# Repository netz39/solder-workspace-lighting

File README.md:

# solder workspace lighting
*Created with KiCad 5.1.9*

Dieses Repo beinhaltet die drei notwendigen Platinen, um den Lötarbeitsplatz im Netz39 ordentlich auszuleuchten.

## central_control
Überwacht die Temperatur aller LED-Projektoren und betreibt PWM-Dimming. Desweiteren bietet die Platine mehrere Schnittstellen (UART, SPI, I²C, CAN) für Erweiterungen an

## constant_current_source
Ein Buck-Converter liefert den voreingestellten konstanten Strom für die LEDs.

## high_power_LED:
Bestückt mit HighPower-LEDs, Thermistor und Kühlkörper.

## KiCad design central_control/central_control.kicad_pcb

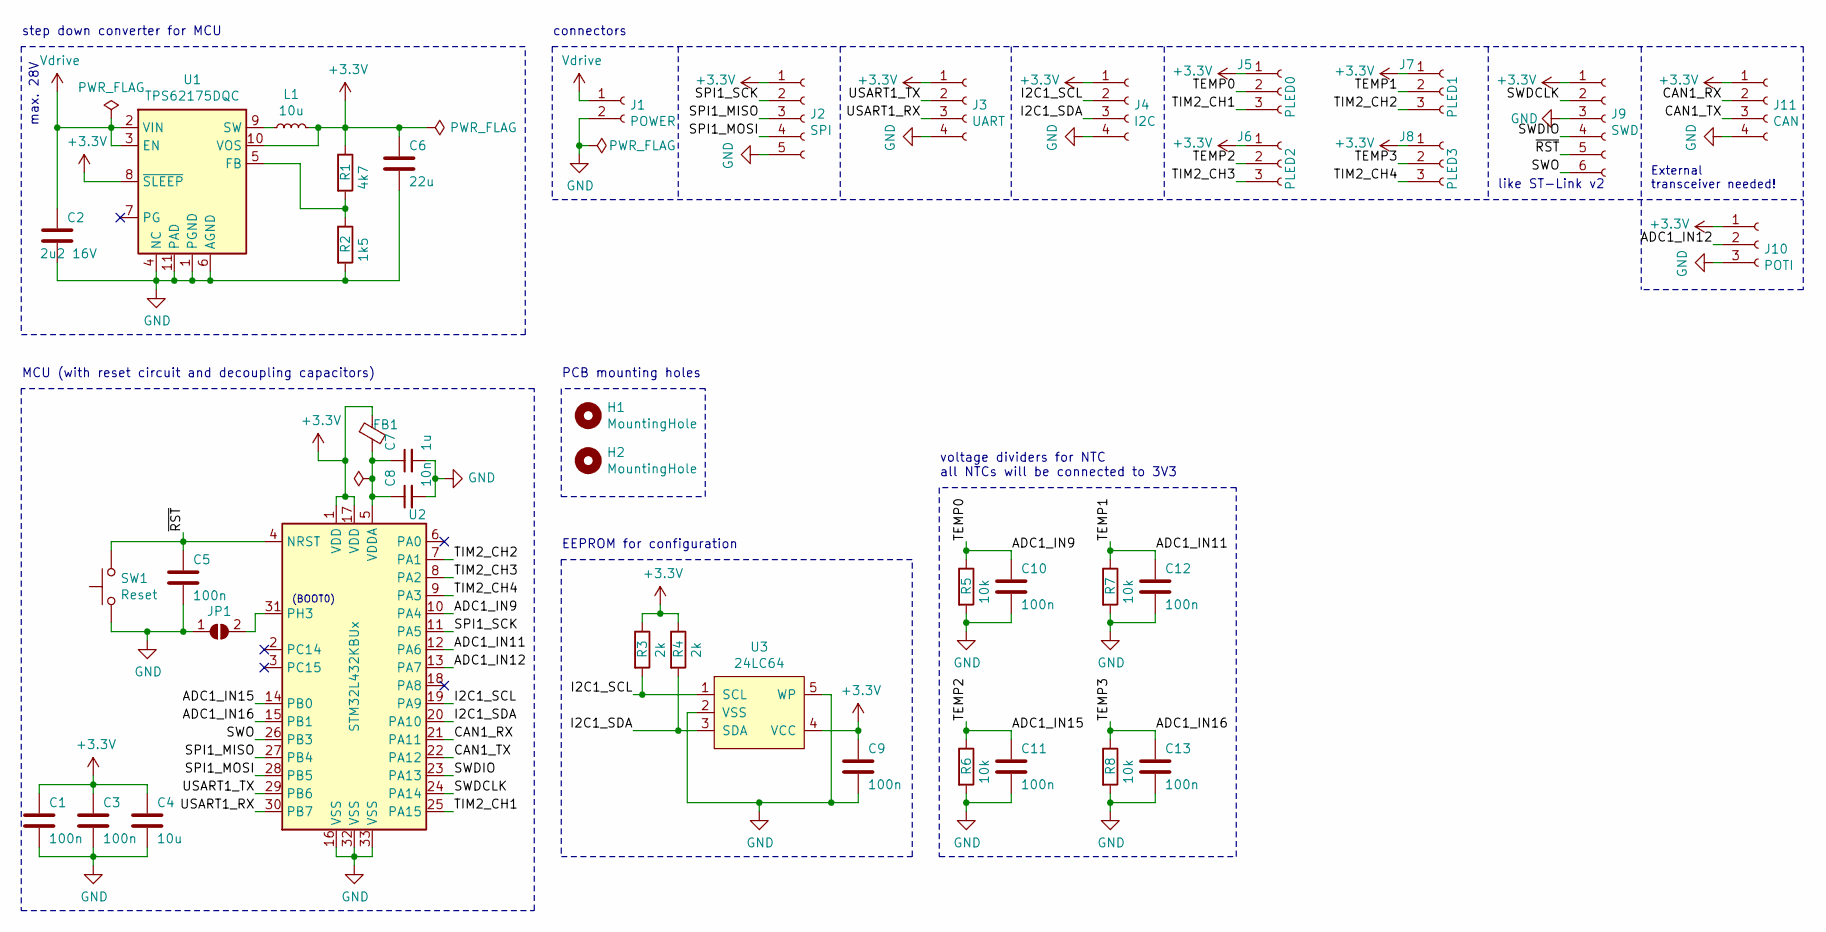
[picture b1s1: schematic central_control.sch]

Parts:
C1, C3, C5, C9, C10, C11, C12, C13: 100n; C_0603_1608Metric
C2: 2u2 16V; C_0603_1608Metric
C4: 10u; C_0805_2012Metric
C6: 22u; C_0805_2012Metric
C7: 1u; C_0603_1608Metric
C8: 10n; C_0603_1608Metric
FB1: Ferrite_Bead_Small; R_0603_1608Metric
H1, H2: MountingHole; MountingHole_2.7mm_M2.5_ISO14580
J1: POWER; Molex_PicoBlade_53047-0210_1x02_P1.25mm_Vertical
J2: SPI; Molex_PicoBlade_53047-0510_1x05_P1.25mm_Vertical
J3: UART; Molex_PicoBlade_53047-0410_1x04_P1.25mm_Vertical
J4: I2C; Molex_PicoBlade_53047-0410_1x04_P1.25mm_Vertical
J5: PLED0; Molex_PicoBlade_53047-0310_1x03_P1.25mm_Vertical
J6: PLED2; Molex_PicoBlade_53047-0310_1x03_P1.25mm_Vertical
J7: PLED1; Molex_PicoBlade_53047-0310_1x03_P1.25mm_Vertical
J8: PLED3; Molex_PicoBlade_53047-0310_1x03_P1.25mm_Vertical
J9: SWD; PinHeader_1x06_P2.54mm_Vertical
J10: POTI; Molex_PicoBlade_53047-0310_1x03_P1.25mm_Vertical
J11: CAN; Molex_PicoBlade_53047-0410_1x04_P1.25mm_Vertical
JP1: SolderJumper_2_Open; SolderJumper-2_P1.3mm_Open_TrianglePad1.0x1.5mm
L1: 10u; L_1210_3225Metric
R1: 4k7; R_0603_1608Metric
R2: 1k5; R_0603_1608Metric
R3, R4: 2k; R_0603_1608Metric
R5, R6, R7, R8: 10k; R_0603_1608Metric
SW1: SW_Push; PTS636_F-leads
U1: TPS62175DQC; WSON-10-1EP_2x3mm_P0.5mm_EP0.84x2.4mm_ThermalVias
U2: STM32L432KBUx; QFN-32-1EP_5x5mm_P0.5mm_EP3.45x3.45mm
U3: 24LC64; SOT-23-5

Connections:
+3V3: C1.1, C3.1, C4.1, C6.1, C9.1, FB1.1, J2.1, J3.1, J4.1, J5.1, J6.1, J7.1, J8.1, J9.1, J10.1, J11.1, L1.2, R1.1, R3.1, R4.1, U1.8 (~SLEEP), U1.10 (VOS), U2.1 (VDD), U2.17 (VDD), U3.4 (VCC)
/ADC1_IN9: C10.1, J5.2, R5.1, U2.10 (PA4)
/ADC1_IN11: C12.1, J7.2, R7.1, U2.12 (PA6)
/ADC1_IN12: J10.2, U2.13 (PA7)
/ADC1_IN15: C11.1, J6.2, R6.1, U2.14 (PB0)
/ADC1_IN16: C13.1, J8.2, R8.1, U2.15 (PB1)
/CAN1_RX: J11.2, U2.21 (PA11)
/CAN1_TX: J11.3, U2.22 (PA12)
/I2C1_SCL: J4.2, R3.2, U2.19 (PA9), U3.1 (SCL)
/I2C1_SDA: J4.3, R4.2, U2.20 (PA10), U3.3 (SDA)
/SPI1_MISO: J2.3, U2.27 (PB4)
/SPI1_MOSI: J2.4, U2.28 (PB5)
/SPI1_SCK: J2.2, U2.11 (PA5)
/SWDCLK: J9.2, U2.24 (PA14)
/SWDIO: J9.4, U2.23 (PA13)
/SWO: J9.6, U2.26 (PB3)
/TIM2_CH1: J5.3, U2.25 (PA15)
/TIM2_CH2: J7.3, U2.7 (PA1)
/TIM2_CH3: J6.3, U2.8 (PA2)
/TIM2_CH4: J8.3, U2.9 (PA3)
/USART1_RX: J3.3, U2.30 (PB7)
/USART1_TX: J3.2, U2.29 (PB6)
/~RST: C5.1, J9.5, SW1.2, U2.4 (NRST)
GND: C1.2, C2.2, C3.2, C4.2, C5.2, C6.2, C7.2, C8.2, C9.2, C10.2, C11.2, C12.2, C13.2, J1.2, J2.5, J3.4, J4.4, J9.3, J10.3, J11.4, JP1.1 (A), R2.2, R5.2, R6.2, R7.2, R8.2, SW1.1, U1.1 (PGND), U1.4 (NC), U1.6 (AGND), U1.11 (PAD), U2.16 (VSS), U2.32 (VSS), U2.33 (VSS), U3.2 (VSS), U3.5 (WP)
unnamed: C7.1, C8.1, FB1.2, U2.5 (VDDA)
unnamed: JP1.2 (B), U2.31 (PH3)
unnamed: L1.1, U1.9 (SW)
unnamed: R1.2, R2.1, U1.5 (FB)
Vdrive: C2.1, J1.1, U1.2 (VIN), U1.3 (EN)

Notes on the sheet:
max. 28V
step down converter for MCU
MCU (with reset circuit and decoupling capacitors)
connectors
PCB mounting holes
External transceiver needed!
EEPROM for configuration
voltage dividers for NTC all NTCs will be connected to 3V3
like ST-Link v2
(BOOT0)

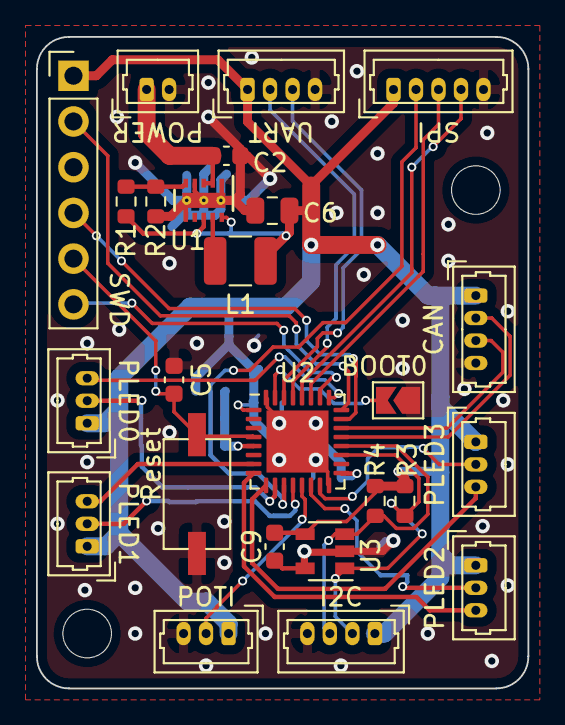
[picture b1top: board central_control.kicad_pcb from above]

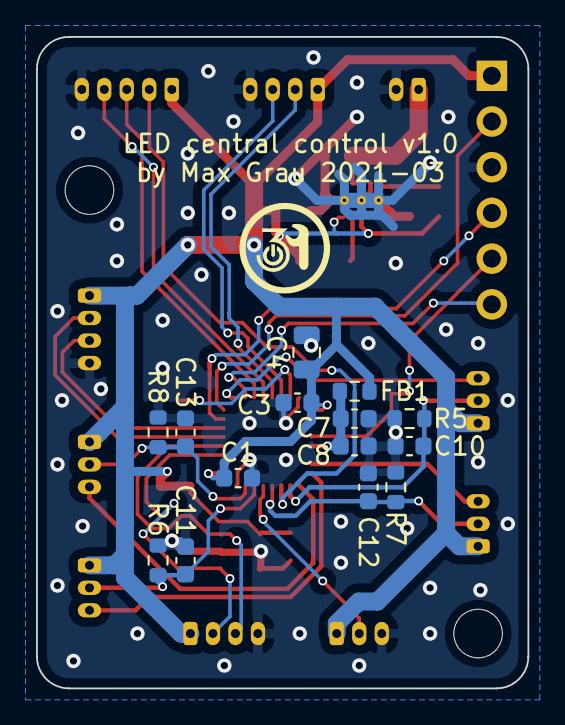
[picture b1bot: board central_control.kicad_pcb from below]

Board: 2 copper layers, 27.3 x 36.2 mm, 42 parts (15 on the bottom side), 29 nets.

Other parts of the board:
svg2mod: G***; netz39-logo

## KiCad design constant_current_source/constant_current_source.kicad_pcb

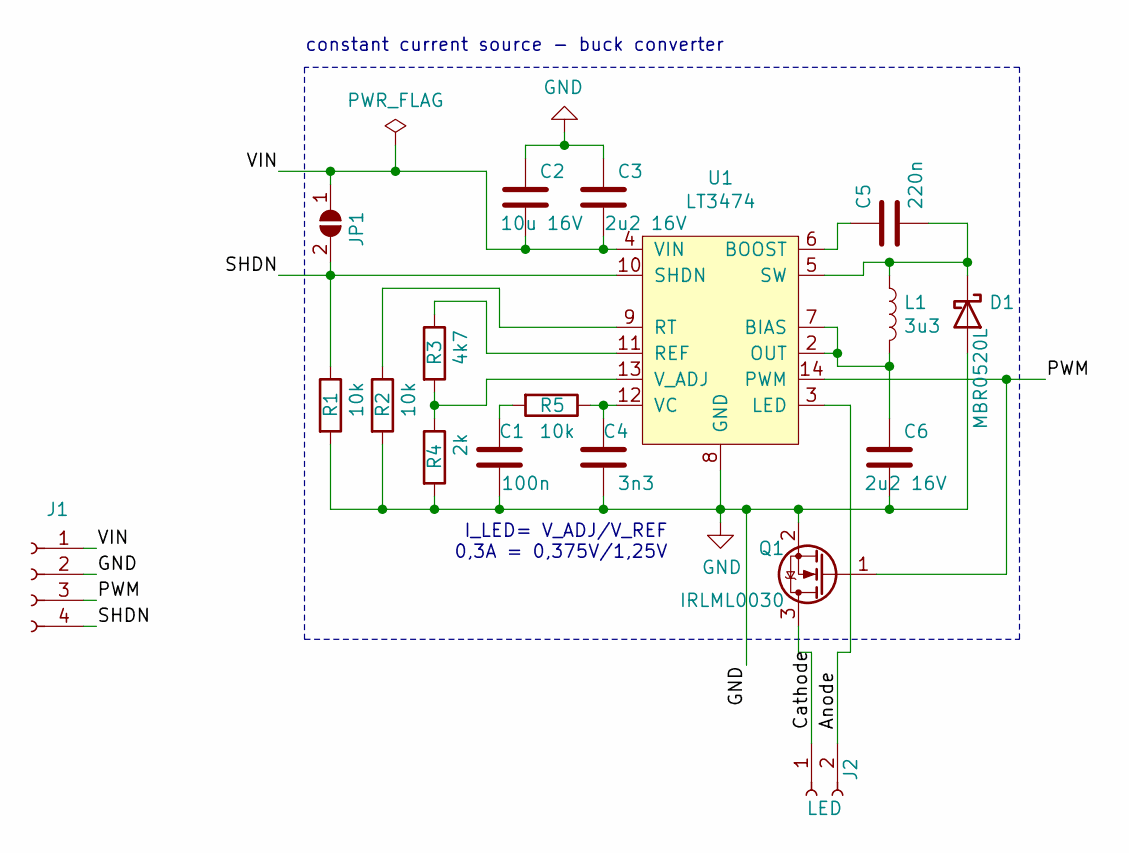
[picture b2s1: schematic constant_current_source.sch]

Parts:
C1: 100n; C_0603_1608Metric
C2: 10u 16V; C_0805_2012Metric
C3, C6: 2u2 16V; C_0603_1608Metric
C4: 3n3; C_0603_1608Metric
C5: 220n; C_0603_1608Metric
D1: MBR0520L; D_SOD-123
J1: Conn; Molex_PicoBlade_53047-0410_1x04_P1.25mm_Vertical
J2: LED; PinHeader_1x02_P2.54mm_Vertical
JP1: SolderJumper_2_Open; SolderJumper-2_P1.3mm_Open_TrianglePad1.0x1.5mm
L1: 3u3; L_Abracon_ASPI-3012S
Q1: IRLML0030; SOT-23
R1, R2, R5: 10k; R_0603_1608Metric
R3: 4k7; R_0603_1608Metric
R4: 2k; R_0603_1608Metric
U1: LT3474; TSSOP-16-1EP_4.4x5mm_P0.65mm

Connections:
/Anode: J2.2, U1.3 (LED)
/Cathode: J2.1, Q1.3 (D)
/PWM: J1.3, Q1.1 (G), U1.14 (PWM)
/SHDN: J1.4, JP1.2 (B), R1.1, U1.10 (SHDN)
/VIN: C2.2, C3.2, J1.1, JP1.1 (A), U1.4 (VIN)
GND: C1.1, C2.1, C3.1, C4.1, C6.2, D1.2 (A), J1.2, Q1.2 (S), R1.2, R2.2, R4.2, U1.8 (GND), U1.15 (GND), U1.17 (GND)
unnamed: C1.2, R5.2
unnamed: C4.2, R5.1, U1.12 (VC)
unnamed: C5.1, U1.6 (BOOST)
unnamed: C5.2, D1.1 (K), L1.1, U1.5 (SW)
unnamed: C6.1, L1.2, U1.2 (OUT), U1.7 (BIAS)
unnamed: R2.1, U1.9 (RT)
unnamed: R3.1, U1.11 (REF)
unnamed: R3.2, R4.1, U1.13 (V_ADJ)

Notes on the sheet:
I_LED= V_ADJ/V_REF 0,3A = 0,375V/1,25V
constant current source - buck converter

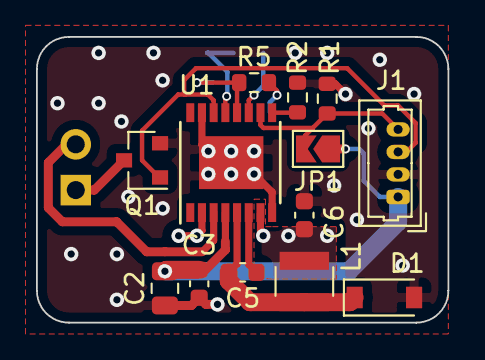
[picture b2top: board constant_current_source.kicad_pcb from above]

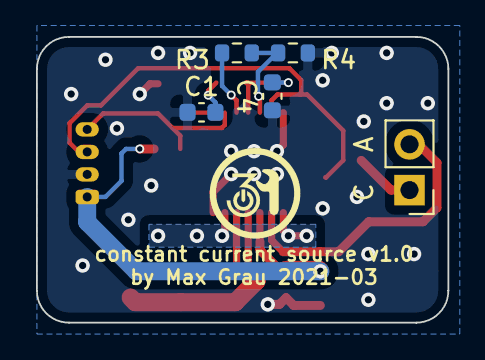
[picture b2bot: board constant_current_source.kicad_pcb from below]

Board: 2 copper layers, 22.9 x 15.9 mm, 19 parts (6 on the bottom side), 14 nets.

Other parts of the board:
svg2mod: G***; netz39-logo

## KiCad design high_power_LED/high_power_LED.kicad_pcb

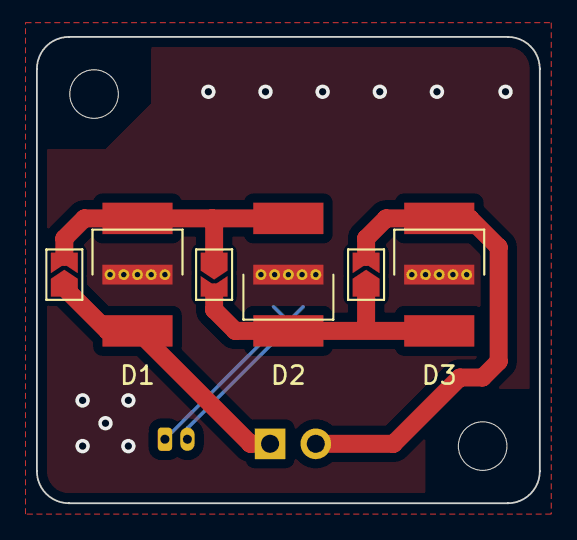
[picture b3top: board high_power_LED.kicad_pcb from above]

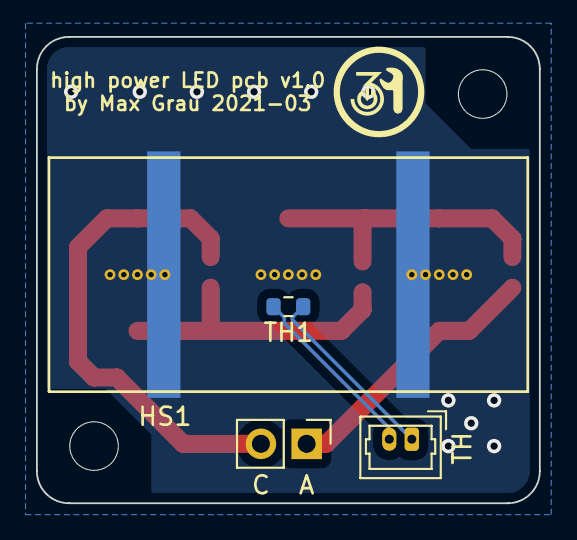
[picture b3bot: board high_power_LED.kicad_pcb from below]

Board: 2 copper layers, 27.9 x 25.9 mm, 13 parts (5 on the bottom side), 7 nets.

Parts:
D1, D2, D3: LED_PAD; Cree-XLamp-MX6
H1, H2: MountingHole; MountingHole_2.7mm_M2.5_ISO14580
HS1: Heatsink_Pad; Heatsink_AAVID_573300D00010G_TO-263
J1: LED; PinHeader_1x02_P2.54mm_Vertical
J2: TH; Molex_PicoBlade_53047-0210_1x02_P1.25mm_Vertical
JP1, JP2, JP3: SolderJumper_2_Open; SolderJumper-2_P1.3mm_Open_TrianglePad1.0x1.5mm
TH1: Thermistor; R_0603_1608Metric
svg2mod: G***; netz39-logo

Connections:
/Anode: D1.2, J1.1, JP1.1
/Cathode: D3.1, J1.2, JP3.2
/TH+: J2.1, TH1.1
/TH-: J2.2, TH1.2
unnamed: D1.1, D2.2, JP1.2, JP2.1
unnamed: D1.3, D2.3, D3.3, HS1.1
unnamed: D2.1, D3.2, JP2.2, JP3.1

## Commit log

2021-02-05 Add constant current source
2021-02-07 Add datasheet and footprint to LT3474
2021-02-07 Add PWM dimming
2021-02-07 Choose STM32L011D3
2021-02-15 Finish sheets
2021-02-16 Fix mosfet symbol
2021-02-17 Add STM32G0 microcontroller
2021-02-17 Replace MCU and add CAN Flexible Datarate. Close #1
2021-02-17 Add 24LC64 small variant
2021-02-17 Add EEPROM for configuration's sake
2021-02-18 Add voltage dividers for temperature measurement and optional connector for poti
2021-02-20 Replace MCU again (with STM32L431KB) STM32G0B1 is not available on digikey/mouser
2021-02-22 Update MCU
2021-02-26 Annotate sheets and assign symbols
2021-03-02 Split project into individual projects and reannotate sheets
2021-03-02 Add N39 logo
2021-03-02 Finish high power led pcb
2021-03-02 Move projects into subfolders
2021-03-02 See commit before
2021-03-02 Finish constant current source pcb
2021-03-05 Finish central control PCB
2021-03-11 „README.md“ ändern
